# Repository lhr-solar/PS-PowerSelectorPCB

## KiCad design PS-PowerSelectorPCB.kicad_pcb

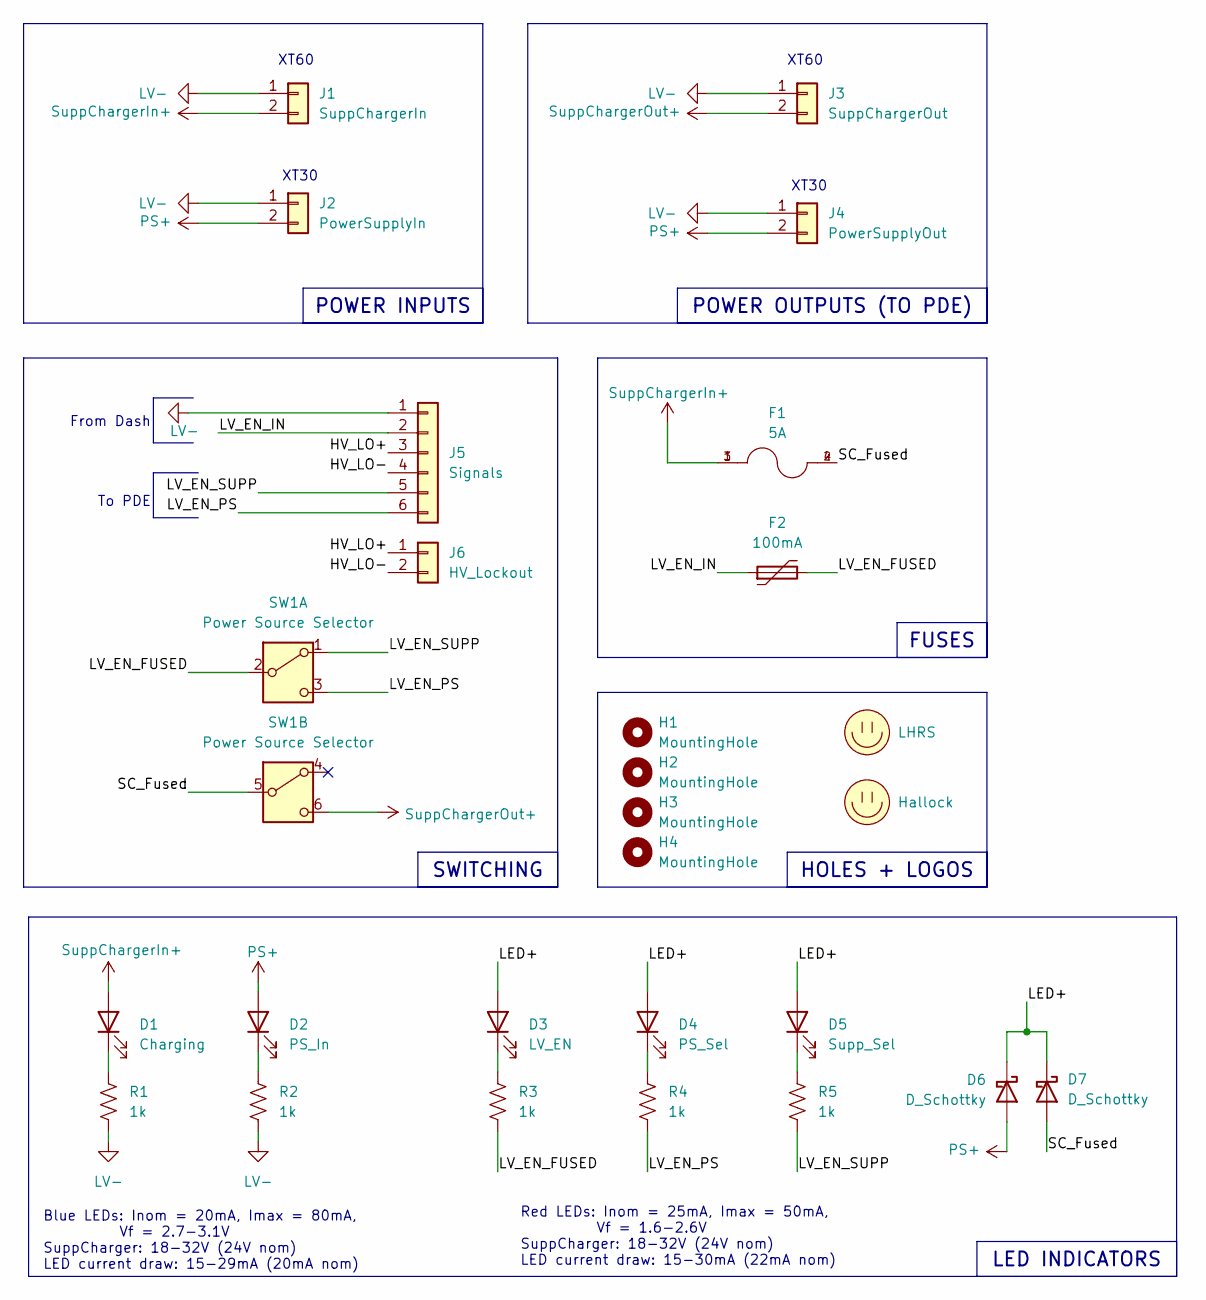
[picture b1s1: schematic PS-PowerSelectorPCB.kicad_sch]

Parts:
D1: Charging; LED_0603_1608Metric_Pad1.05x0.95mm_HandSolder
D2: PS_In; LED_0603_1608Metric_Pad1.05x0.95mm_HandSolder
D3: LV_EN; LED_0603_1608Metric_Pad1.05x0.95mm_HandSolder
D4: PS_Sel; LED_0603_1608Metric_Pad1.05x0.95mm_HandSolder
D5: Supp_Sel; LED_0603_1608Metric_Pad1.05x0.95mm_HandSolder
D6, D7: D_Schottky; D_SOD-123
F1: 5A; FUSE_3568
F2: 100mA; Fuse_1210_3225Metric_Pad1.42x2.65mm_HandSolder
H1, H2, H3, H4: MountingHole; MountingHole_3.2mm_M3
J1: SuppChargerIn; AMASS_XT60-M_1x02_P7.20mm_Vertical
J2: PowerSupplyIn; AMASS_XT30UPB-M_1x02_P5.0mm_Vertical
J3: SuppChargerOut; AMASS_XT60-M_1x02_P7.20mm_Vertical
J4: PowerSupplyOut; AMASS_XT30UPB-M_1x02_P5.0mm_Vertical
J5: Signals; Molex_Nano-Fit_105309-xx06_1x06_P2.50mm_Vertical
J6: HV_Lockout; Molex_Nano-Fit_105309-xx02_1x02_P2.50mm_Vertical
LOGO1: LHRS; LHRs_LOGO
LOGO2: Hallock; Hallock_Image_Tiny
R1, R2, R3, R4, R5: 1k; R_0603_1608Metric_Pad0.98x0.95mm_HandSolder
SW1: Power Source Selector; 100DP1T2B4VS2QE

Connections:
/HV_LO+: J5.3, J6.1
/HV_LO-: J5.4, J6.2
/LED+: D3.2 (A), D4.2 (A), D5.2 (A), D6.1 (K), D7.1 (K)
/LV_EN_FUSED: F2.2, R3.2, SW1.2 (B)
/LV_EN_IN: F2.1, J5.2
/LV_EN_PS: J5.6, R4.2, SW1.3 (C)
/LV_EN_SUPP: J5.5, R5.2, SW1.1 (A)
/SC_Fused: D7.2 (A), F1.2, F1.4, SW1.5 (B)
LV-: J1.1, J2.1, J3.1, J4.1, J5.1, R1.2, R2.2
unnamed: D1.1 (K), R1.1
unnamed: D2.1 (K), R2.1
unnamed: D3.1 (K), R3.1
unnamed: D4.1 (K), R4.1
unnamed: D5.1 (K), R5.1
PS+: D2.2 (A), D6.2 (A), J2.2, J4.2
SuppChargerIn+: D1.2 (A), F1.1, F1.3, J1.2
SuppChargerOut+: J3.2, SW1.6 (C)

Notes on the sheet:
Blue LEDs: Inom = 20mA, Imax = 80mA, Vf = 2.7-3.1V SuppCharger: 18-32V (24V nom) LED current draw: 15-29mA (20mA nom)
Red LEDs: Inom = 25mA, Imax = 50mA, Vf = 1.6-2.6V SuppCharger: 18-32V (24V nom) LED current draw: 15-30mA (22mA nom)
To PDE
XT60
XT30
From Dash
LED INDICATORS
SWITCHING
POWER INPUTS
FUSES
HOLES + LOGOS
POWER OUTPUTS (TO PDE)

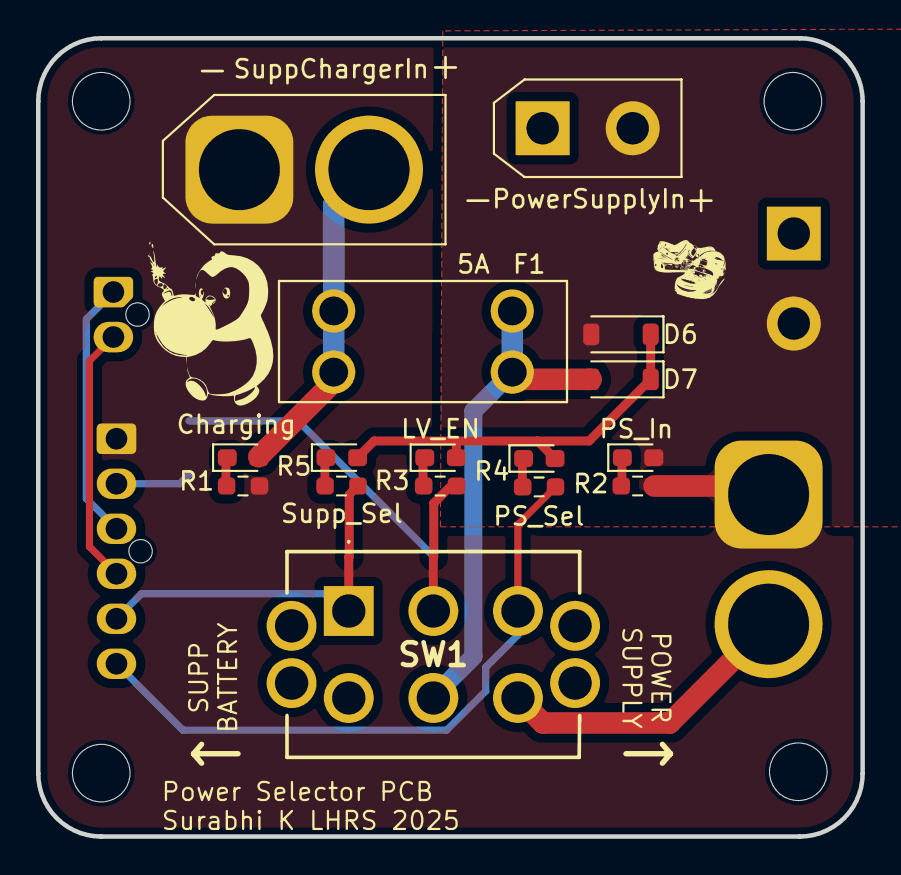
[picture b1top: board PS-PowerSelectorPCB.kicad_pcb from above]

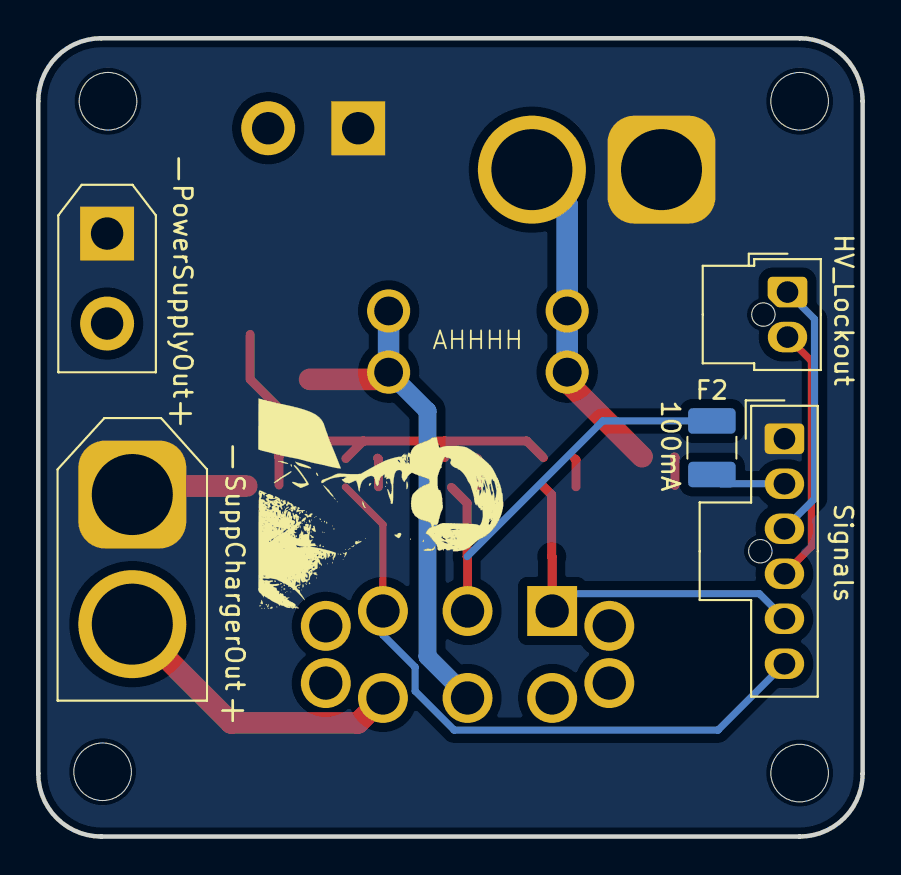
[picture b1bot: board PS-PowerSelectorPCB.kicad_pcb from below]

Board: 2 copper layers, 45.8 x 44.3 mm, 27 parts (6 on the bottom side), 17 nets.

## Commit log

2025-09-12 init
2025-09-13 new pinouts
2025-10-12 initial schematic
2025-10-14 initial layout
2025-10-14 fixed switch footprint + silkscreen
2025-10-14 fixed 3d models
2025-10-14 silkscreens
2025-10-14 gerbers + fixes
2025-10-14 filled zones
2025-10-18 added step
2025-10-25 bomb
